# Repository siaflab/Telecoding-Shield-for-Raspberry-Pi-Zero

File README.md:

# Telecoding-Shield-for-Raspberry-Pi-Zero
Telecoding Shield for Raspberry Pi Zero is a board that can mount 920 MHz band LoRa module, OSD and DAC chip.
Power supply to Raspberry Pi Zero can also be done from this shield in the range of 5V to 14V.
If you change the grade of the DC - DC converter, such as changing from Murata's "OKL-T/3-W12N-C" to "OKL-T/6-W12N-C", 
you can select the current value required for your system. The current can be supplied up to 6 A, it is possible to operate rasberry pi 3.
This Shield successfully communicated between the ground and the stratosphere in our <a href="http://space-moere.org">project</a>.

## REQUIREMENT
- raspberry pi zero

## DEPENDENCIES
- OSD chip: [MAX7456](https://datasheets.maximintegrated.com/en/ds/MAX7456.pdf)
- DAC chip: [PCM5102](http://masterandrey.com/files/pcm5102.pdf)

This board can mount either of the following LoRa modules.
The frequency with LoRa's unlicensed band can communicate varies depending on the country's rule.
- [interplan IM920C](http://www.interplan.co.jp)
- [rflink RM-92A](http://www.rflink.co.jp/)

Refer to the <a href="https://www.homepage-tukurikata.com/">partslist</a> for other mounting parts.

## CREDIT
Telecoding Shield for Raspberry Pi Zero licensed under MIT License.  
https://github.com/siaflab/Telecoding-Shield-for-Raspberry-Pi-Zero

Space Moere Project  
ARTSAT x SIAF Lab  
http://space-moere.org

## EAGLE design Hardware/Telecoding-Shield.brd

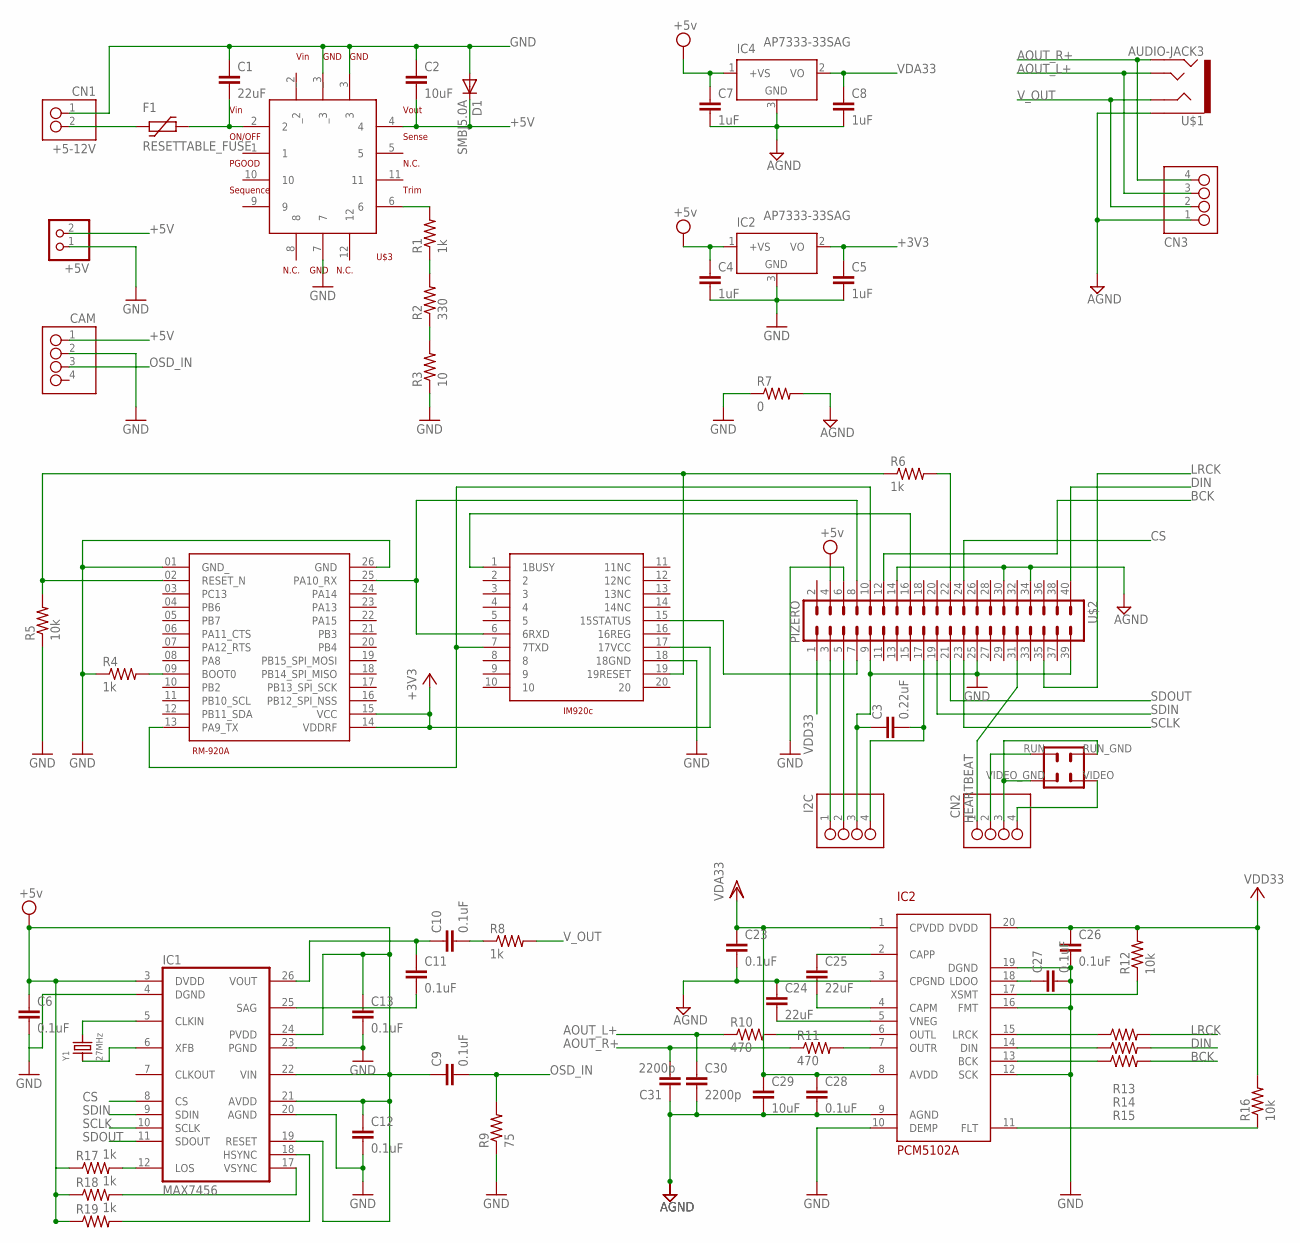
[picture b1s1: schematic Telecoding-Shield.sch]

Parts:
+5V: PINHD-1X2; 1X02
C1, C24, C25: 22uF; 0805
C2, C29: 10uF; 0805
C3: 0.22uF; 0805
C4, C5, C7, C8: 1uF; 0805
C6, C9, C10, C11, C12, C13, C23, C26, C27, C28: 0.1uF; 0805
C30, C31: 2200p; 0805
CAM: SM04B-SRSS-TB
CN1: +5-12V; SM02B-SRSS-TB
CN2, CN3: SM04B-SRSS-TB
D1: SMBJ5.0A; SMA
F1: RESETTABLE_FUSE; 1812L
I2C: SM04B-SRSS-TB
IC1: MAX7456; TSSOP28
IC2, IC4: AP7333-33SAG; SOT23
IC3: PCM5102; TSSOP20
R1, R4, R6, R8, R17, R18, R19: 1k; M0805
R2: 330; M0805
R3: 10; M0805
R5, R12, R16: 10k; M0805
R7: 0; M0805
R9: 75; M0805
R10, R11: 470; M0805
R13, R14, R15: 27; M0805
RM-920A: RM-92A_SOCKETBP; RM-92A
U$1: AUDIO-JACK3; AUDIO-JACK-TRRS-SMD
U$2: PIZERO; PIZERO_THOUGH_HOLE
U$3: MURATA_OKL_T6_W12
U$7: IM920C
Y1: 27MHz; ABS07

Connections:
+3V3: C5.1, IC2.2 (VO), RM-920A.14 (VDDRF), RM-920A.15 (VCC), U$7.17 (17VCC)
+5V: +5V.2, C2.2, C4.1, C6.1, C7.1, C9.1, C12.1, C13.1, CAM.1, D1.C, IC1.3 (DVDD), IC1.19 (RESET), IC1.21 (AVDD), IC1.22 (VIN), IC1.24 (PVDD), IC2.1 (+VS), IC4.1 (+VS), R17.1, R18.1, R19.1, U$2.4, U$3.4
AGND: C7.2, C8.2, C23.2, C24.1, C28.2, C29.2, C30.2, C31.1, CN3.1, IC3.3 (CPGND), IC3.9 (AGND), IC4.3 (GND), R7.2, U$1.EARTH, U$2.14, U$2.30, U$2.34, U$3.7
AOUT_L+: C30.1, CN3.3, R10.1, U$1.TIP
AOUT_R+: C31.2, CN3.4, R11.1, U$1.RING2
BCK: R15.2, U$2.12
CS: IC1.8 (CS), U$2.24
DIN: R14.2, U$2.40
GND: +5V.1, C1.1, C2.1, C3.1, C4.2, C5.2, C6.2, C12.2, C13.2, C26.2, C27.2, CAM.2, CN1.1, CN2.3, D1.A, I2C.3, IC1.4 (DGND), IC1.20 (AGND), IC1.23 (PGND), IC2.3 (GND), IC3.10 (DEMP), IC3.12 (SCK), IC3.16 (FMT), IC3.19 (DGND), R3.1, R4.1, R5.1, R7.1, R9.1, RM-920A.01 (GND_), RM-920A.26 (GND), U$2.6, U$2.9, U$2.25, U$2.39, U$2.RUN_GND, U$2.VIDEO_GND (VIDEOP_GND), U$3.3, U$3._3, U$7.18 (18GND)
HEARTBEAT: CN2.1, U$2.31
LRCK: R13.2, U$2.35
unnamed: R5.2, R6.1, RM-920A.02 (RESET_N), U$7.19 (19RESET)
unnamed: C1.2, F1.2, U$3.2
unnamed: R6.2, U$2.22
unnamed: RM-920A.25 (PA10_RX), U$2.8, U$7.6 (6RXD)
unnamed: R4.2, RM-920A.09 (BOOT0)
unnamed: R2.1, R3.2
unnamed: U$2.7, U$7.15 (15STATUS)
unnamed: U$2.16, U$7.1 (1BUSY)
unnamed: R1.1, R2.2
unnamed: R1.2, U$3.6
unnamed: CN2.4, U$2.VIDEO
unnamed: IC1.5 (CLKIN), Y1.2
unnamed: RM-920A.13 (PA9_TX), U$2.10, U$7.7 (7TXD)
unnamed: CN1.2, F1.1
unnamed: IC1.6 (XFB), Y1.1
unnamed: IC1.12 (LOS), R17.2
unnamed: IC1.17 (VSYNC), R18.2
unnamed: IC1.18 (HSYNC), R19.2
unnamed: I2C.1, U$2.3
unnamed: I2C.2, U$2.5
unnamed: C3.2, I2C.4, U$2.17
unnamed: CN2.2, U$2.RUN
unnamed: C10.1, C11.1, IC1.26 (VOUT)
unnamed: C10.2, R8.1
unnamed: C11.2, IC1.25 (SAG)
unnamed: C24.2, IC3.5 (VNEG)
unnamed: C25.1, IC3.2 (CAPP)
unnamed: C25.2, IC3.4 (CAPM)
unnamed: C27.1, IC3.18 (LDOO)
unnamed: IC3.7 (OUTR), R11.2
unnamed: IC3.15 (LRCK), R13.1
unnamed: IC3.6 (OUTL), R10.2
unnamed: IC3.14 (DIN), R14.1
unnamed: IC3.13 (BCK), R15.1
unnamed: IC3.11 (FLT), R16.1
unnamed: IC3.17 (XSMT), R12.1
OSD_IN: C9.2, CAM.3, R9.2
SCLK: IC1.10 (SCLK), U$2.23
SDIN: IC1.9 (SDIN), U$2.19
SDOUT: IC1.11 (SDOUT), U$2.21
VDA33: C8.1, C23.1, C28.1, C29.1, IC3.1 (CPVDD), IC3.8 (AVDD), IC4.2 (VO)
VDD33: C26.1, IC3.20 (DVDD), R12.2, R16.2, U$2.1
V_OUT: CN3.2, R8.2, U$1.RING1

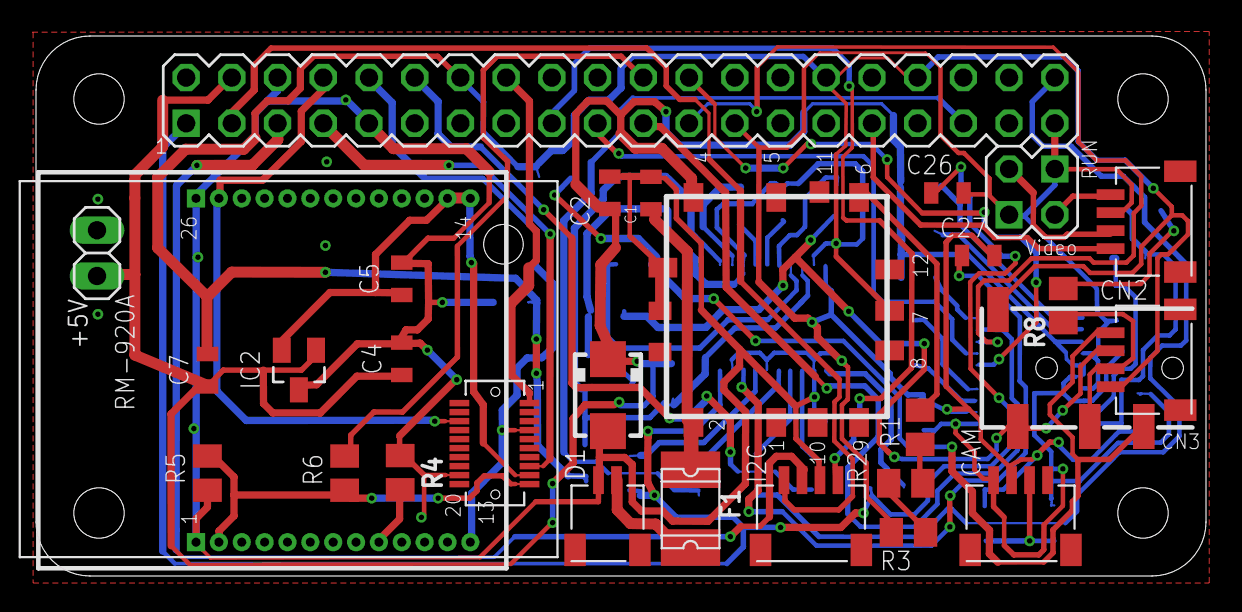
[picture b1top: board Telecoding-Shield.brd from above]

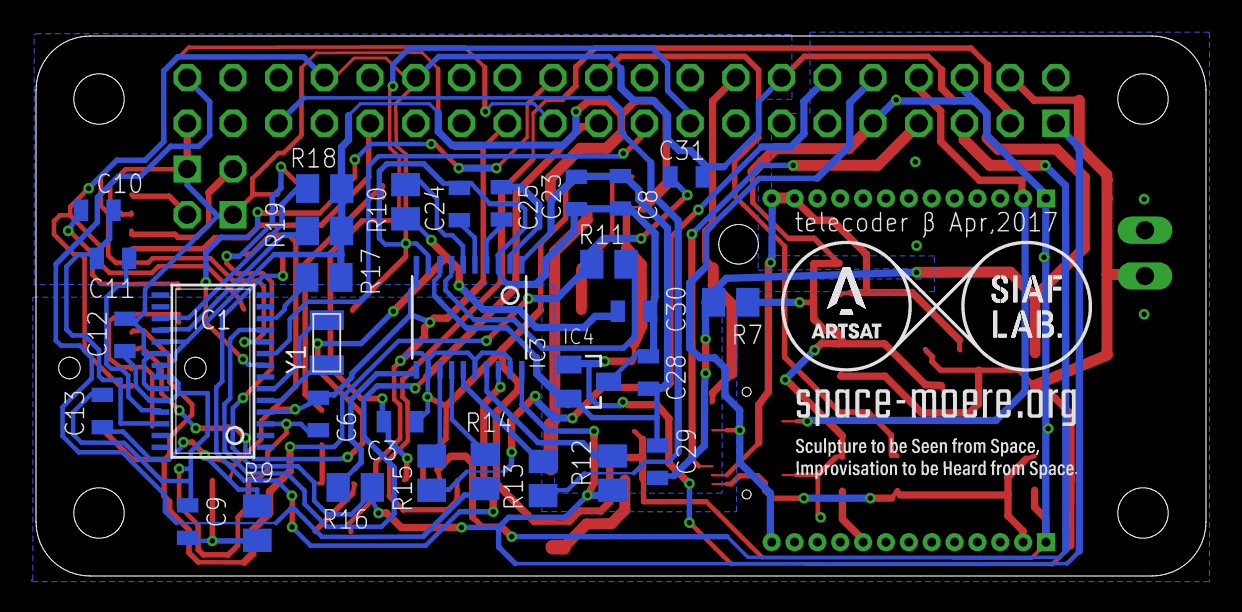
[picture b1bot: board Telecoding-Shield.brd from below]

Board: 2 copper layers, 65.0 x 30.0 mm, 59 parts (31 on the bottom side), 54 nets.

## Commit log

2018-02-28 Create Hardware
2018-02-28 Create test
2018-03-01 Update partslist
2018-03-03 Create LICENSE

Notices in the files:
parts and their libraries:
SparkFun-Capacitors: Licensing: Creative Commons ShareAlike 4.0 International - https://creativecommons.org/licenses/by-sa/4.0
